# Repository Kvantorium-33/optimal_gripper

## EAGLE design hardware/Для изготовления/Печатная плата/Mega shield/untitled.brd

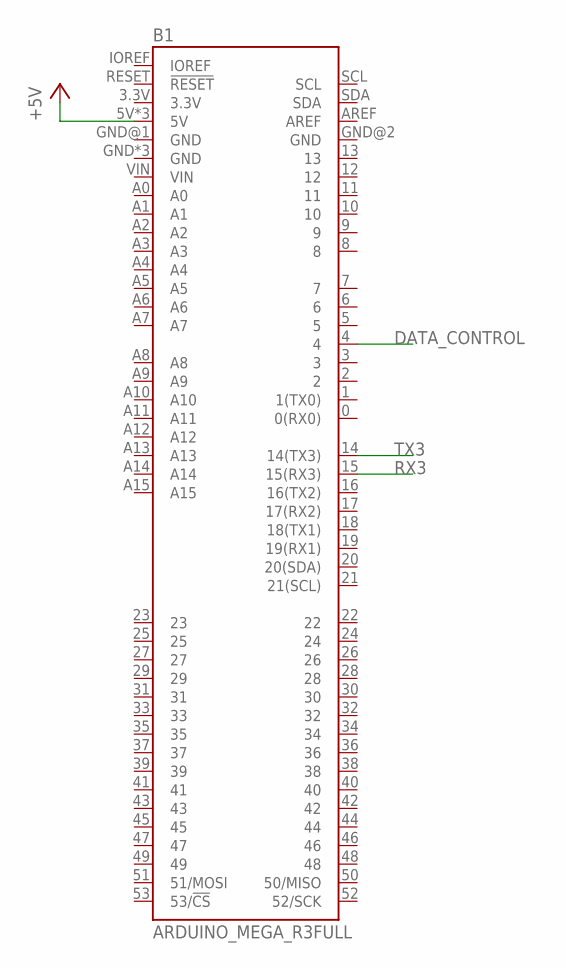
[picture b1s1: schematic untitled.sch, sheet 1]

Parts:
B1: ARDUINO_MEGA_R3FULL; ARDUINO_MEGA_NO_SILK

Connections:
+5V: B1.5V, B1.5V@1 (5V), B1.5V@2 (5V); also elsewhere on the board
DATA_CONTROL: B1.4; also elsewhere on the board
RX3: B1.15 (15(RX3)); also elsewhere on the board
TX3: B1.14 (14(TX3)); also elsewhere on the board

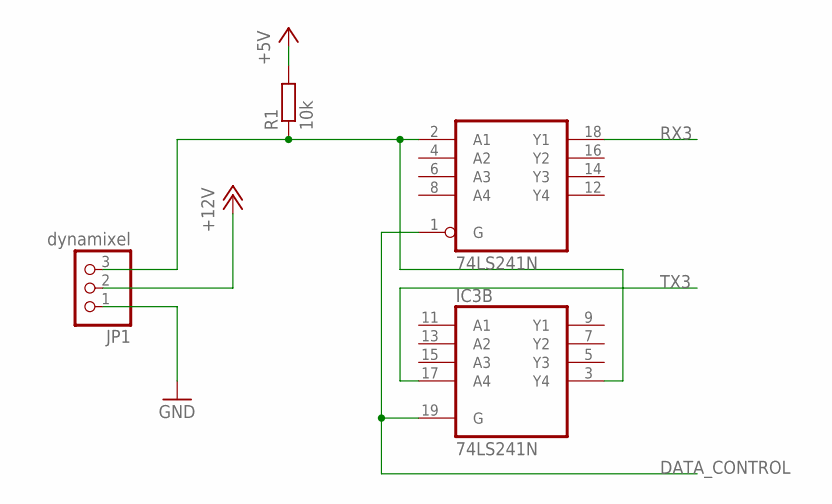
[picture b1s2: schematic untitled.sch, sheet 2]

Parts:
IC3: 74LS241N; DIL20
JP1: dynamixel; 1X03
R1: 10k; 0207/10

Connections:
+5V: R1.2; also elsewhere on the board
+12V: JP1.2
DATA_CONTROL: IC3.1 (G), IC3.19 (G); also elsewhere on the board
GND: IC3.10 (GND), JP1.1
unnamed: IC3.2 (A1), IC3.3 (Y4), JP1.3, R1.1
RX3: IC3.18 (Y1); also elsewhere on the board
TX3: IC3.17 (A4); also elsewhere on the board
VCC: IC3.20 (VCC)

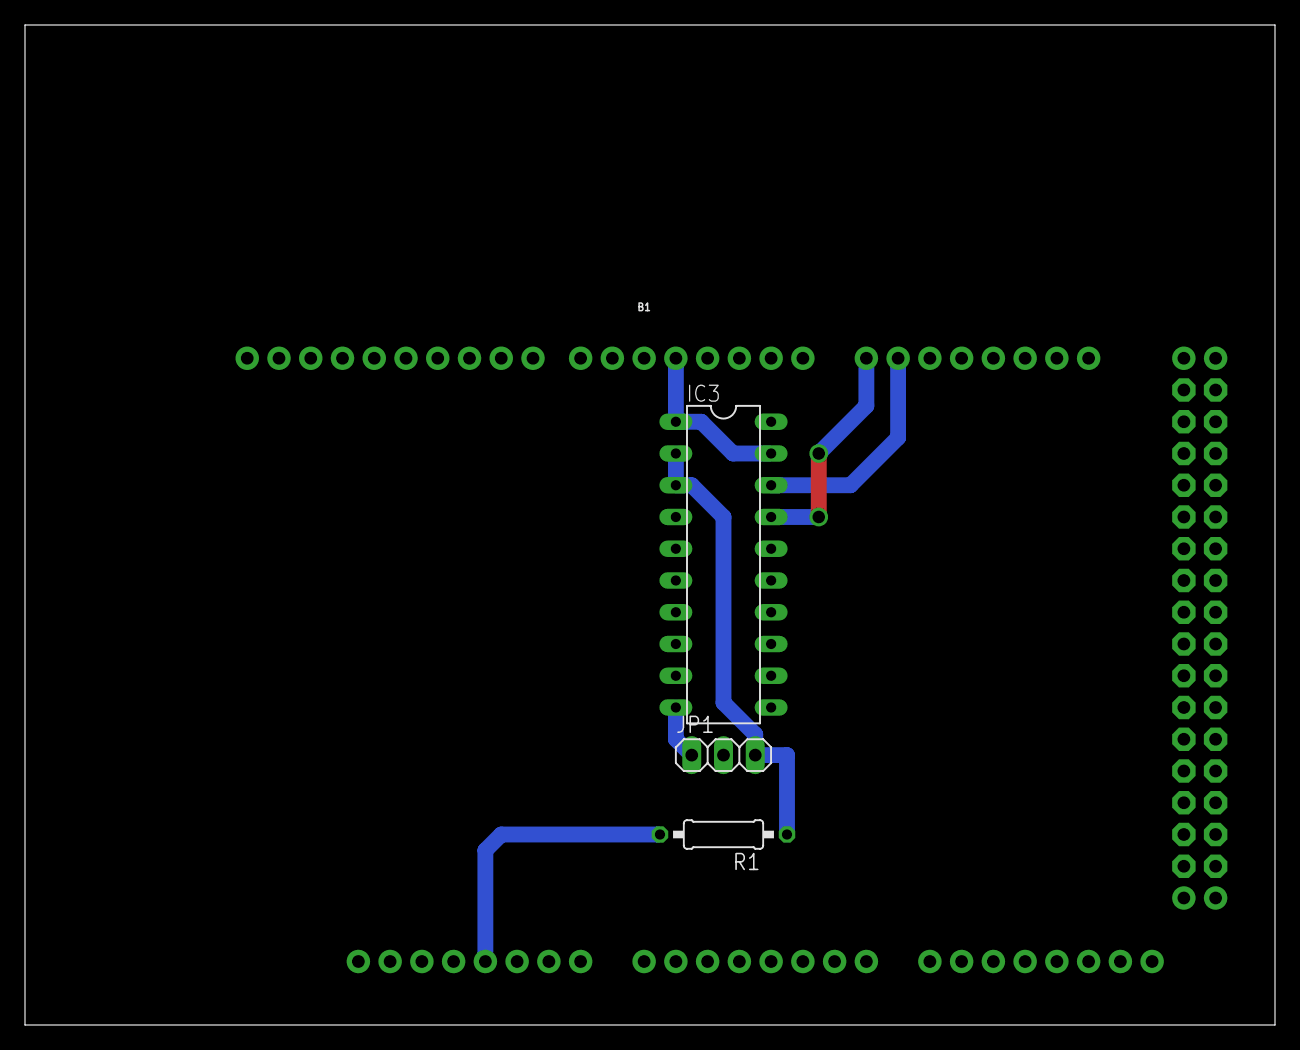
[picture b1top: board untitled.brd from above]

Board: 2 copper layers, 100.0 x 80.0 mm, 4 parts (0 on the bottom side), 6 nets.

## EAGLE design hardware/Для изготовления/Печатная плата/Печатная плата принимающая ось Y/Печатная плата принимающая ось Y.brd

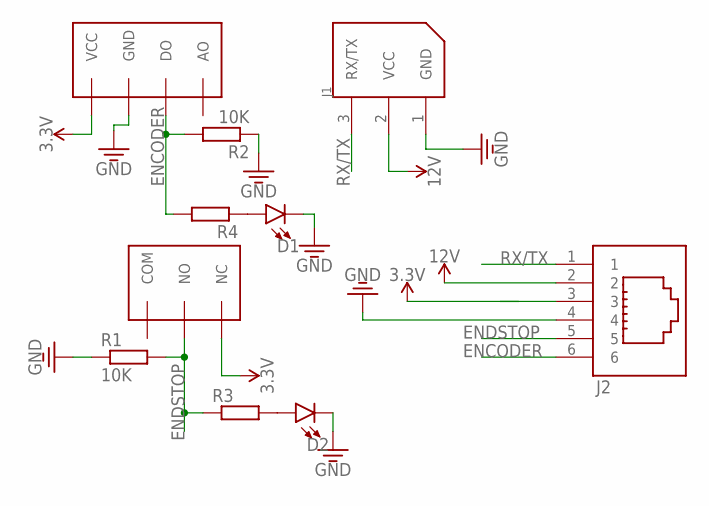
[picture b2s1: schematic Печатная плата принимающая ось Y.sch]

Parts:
D1, D2: LED5MM; LED_5MM
J1: 22-03-5035; 5267-3
J2: 615006138421
R1, R2: 10K; 0204/7
R3, R4: R-EU_0204/7; 0204/7
U$1: OPTICAL_ENCODER_FC-01
U$2: ENDSTOP

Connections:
3.3V: J2.3, U$1.VCC, U$2.NC
12V: J1.2 (VCC), J2.2
ENCODER: J2.6, R2.2, R4.2, U$1.DO
ENDSTOP: J2.5, R1.2, R3.1, U$2.NO
GND: D1.K (C), D2.K (C), J1.1 (GND), J2.4, R1.1, R2.1, U$1.GND
unnamed: D2.A, R3.2
unnamed: D1.A, R4.1
RX/TX: J1.3 (RX/TX), J2.1

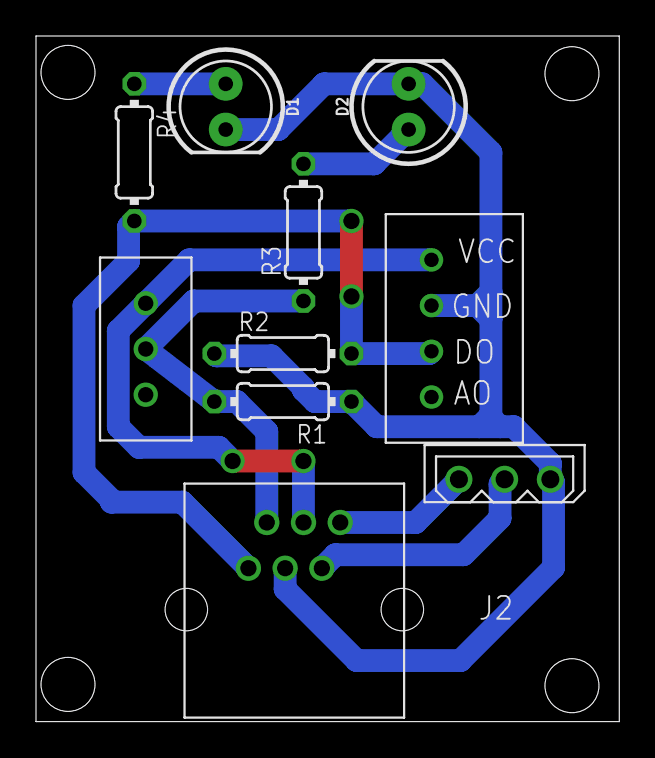
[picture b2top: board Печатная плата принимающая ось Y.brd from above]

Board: 2 copper layers, 32.4 x 38.1 mm, 10 parts (0 on the bottom side), 8 nets.

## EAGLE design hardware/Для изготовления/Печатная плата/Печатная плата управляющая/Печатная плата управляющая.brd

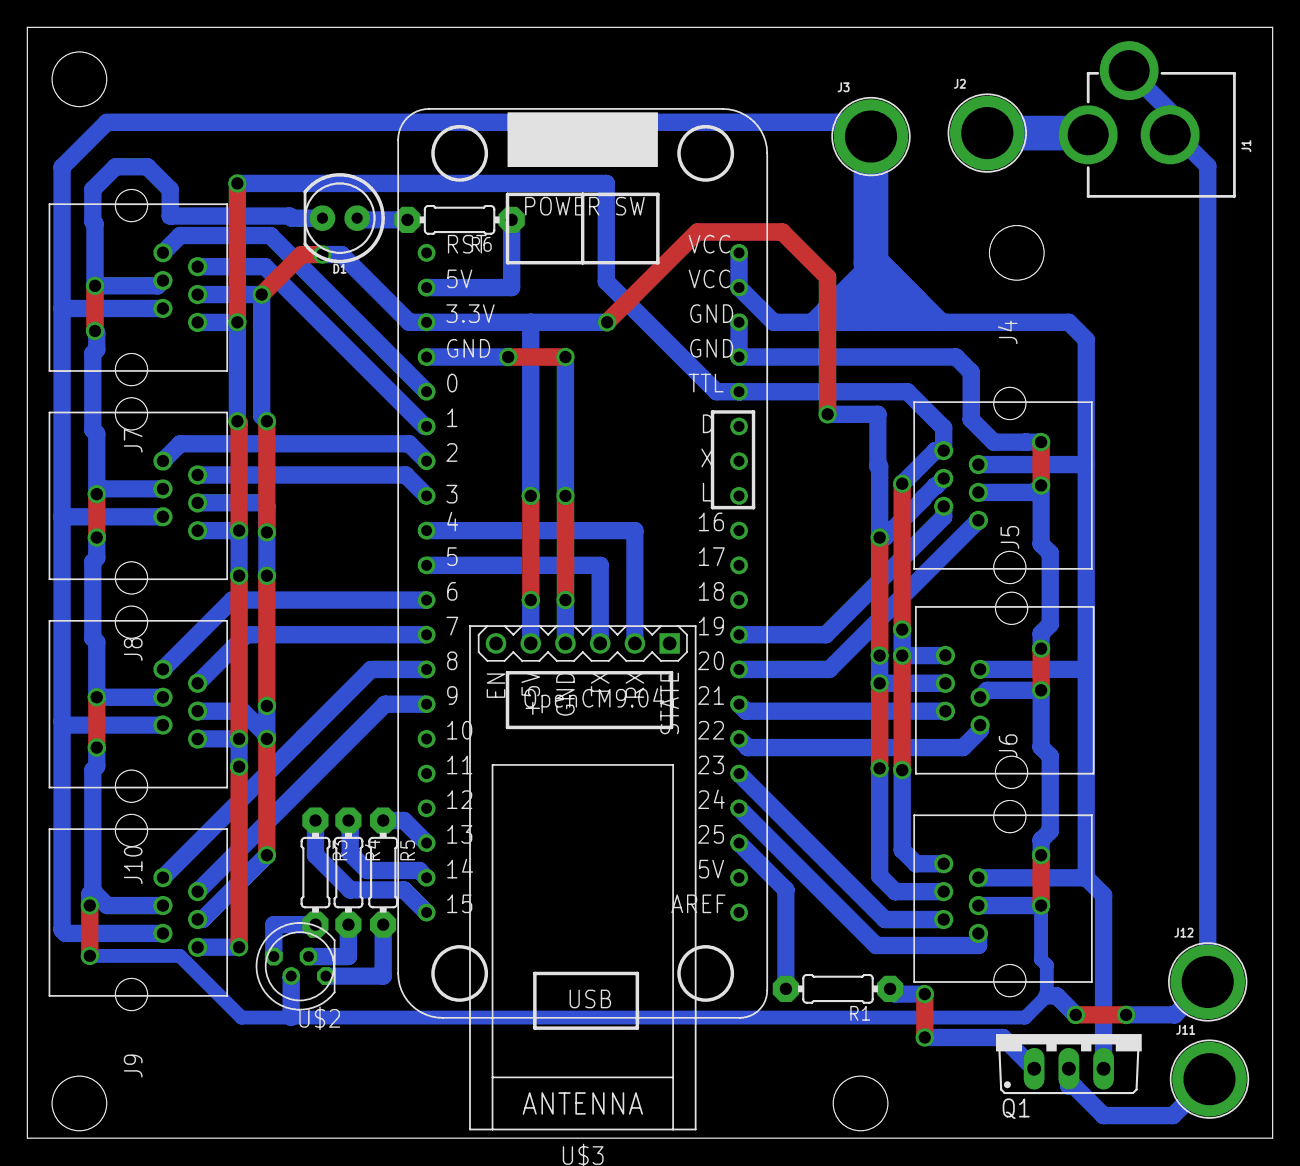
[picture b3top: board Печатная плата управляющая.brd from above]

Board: 2 copper layers, 91.1 x 81.3 mm, 22 parts (0 on the bottom side), 32 nets.

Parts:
D1: LED_5MM
J1: POWER_JACK; POWER_JACK_PTH
J2, J3, J11, J12: BANANA_CONN
J4, J5, J6, J7, J8, J9, J10: 615006138421
Q1: IRF540; TO220BV
R1: 100; 0204/7
R3, R4, R5, R6: 330; 0204/7
U$1: OPENCM9.04
U$2: 5MMRGBLED; LED5MMRGB
U$3: WIRELESS-BLUETOOTH-HC-05

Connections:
3.3V: J4.3, J5.3, J6.3, J7.3, J8.3, J9.3, J10.3, U$1.3.3V, U$3.5
5V: R6.1, U$1.5V, U$1.5V2
12V: J3.P$1, J4.2, J5.2, J6.2, J7.2, J8.2, J9.2, J10.2, Q1.S, U$1.VCC, U$1.VCC2
BLUE: R5.1, U$1.13
ENCODER_X_1: J4.6, U$1.20
ENCODER_X_2: J5.6, U$1.22
ENCODER_Y: J6.6, U$1.24
ENCODER_Z_1: J7.6, U$1.0
ENCODER_Z_2: J8.6, U$1.2
ENCODER_Z_3: J10.6, U$1.6
ENCODER_Z_4: J9.6, U$1.8
ENDSTOP_X_1: J4.5, U$1.19
ENDSTOP_X_2: J5.5, U$1.21
ENDSTOP_Y: J6.5, U$1.23
ENDSTOP_Z_1: J7.5, U$1.1
ENDSTOP_Z_2: J8.5, U$1.3
ENDSTOP_Z_3: J10.5, U$1.7
ENDSTOP_Z_4: J9.5, U$1.9
GND: D1.K, J1.GND, J1.GNDBREAK, J4.4, J5.4, J6.4, J7.4, J8.4, J9.4, J10.4, J12.P$1, U$1.GND, U$1.GND2, U$1.GND3, U$2.P$3, U$3.4
GREEN: R4.1, U$1.14
unnamed: J11.P$1, Q1.D
unnamed: R4.2, U$2.P$2
unnamed: Q1.G, R1.1
unnamed: R5.2, U$2.P$1
unnamed: R3.2, U$2.P$4
unnamed: D1.A, R6.2
unnamed: J1.PWR, J2.P$1
PUMP: R1.2, U$1.25
RED: R3.1, U$1.15
RX2: U$1.5, U$3.3
RX/TX: J4.1, J5.1, J6.1, J7.1, J8.1, J9.1, J10.1, U$1.TTL
TX2: U$1.4, U$3.2

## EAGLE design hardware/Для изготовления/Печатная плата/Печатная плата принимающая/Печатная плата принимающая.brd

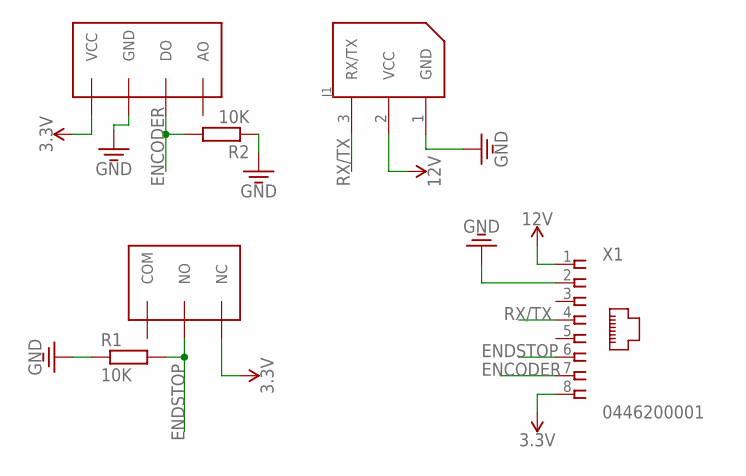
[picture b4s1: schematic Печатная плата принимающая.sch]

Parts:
J1: 22-03-5035; 5267-3
R1, R2: 10K; 0204/7
U$1: OPTICAL_ENCODER_FC-01
U$2: ENDSTOP
X1: 0446200001

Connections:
3.3V: U$1.VCC, U$2.NC, X1.8
12V: J1.2 (VCC), X1.1
ENCODER: R2.2, U$1.DO, X1.7
ENDSTOP: R1.2, U$2.NO, X1.6
GND: J1.1 (GND), R1.1, R2.1, U$1.GND, X1.2
RX/TX: J1.3 (RX/TX), X1.4

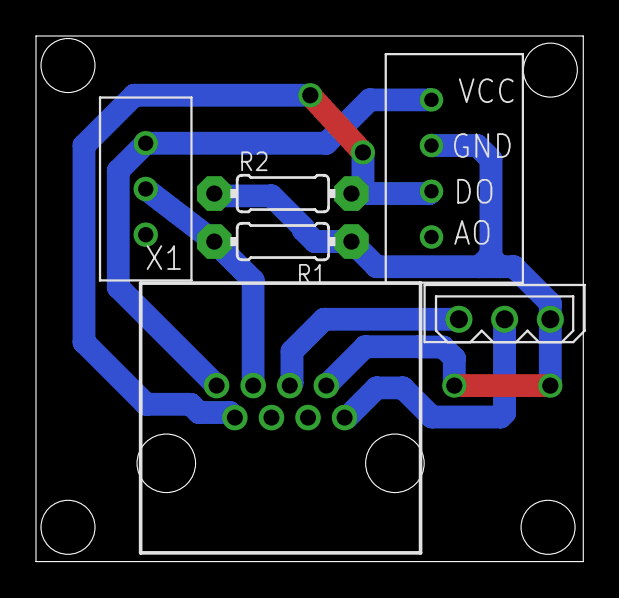
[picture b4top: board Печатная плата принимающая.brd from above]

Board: 2 copper layers, 30.4 x 29.2 mm, 6 parts (0 on the bottom side), 6 nets.

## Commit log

2019-07-16 Добавлены 3D модели
2019-07-16 Подвинул
2019-07-16 1. Изменены каретки
    2. Изменена конструкция манипулятора
    3. Добавлен станочный профиль 30х30х728
2019-07-16 Сортирующая ячейка
2019-07-16 Изменена конструкция кареток оси Х
2019-07-16 Исправлен недочет Фиксатора каретки
2019-07-17 изменена щека каретки
2019-07-17 щека каретки
2019-07-17 Обновлена "сортирующая ячейка"
2019-07-17 Поправлены "Свойства Inventor" деталей
2019-07-18 Added tensorflow ROS package
2019-07-18 изменена сборка
2019-07-18 изменена каретка
2019-07-21 изменена каретка
    центральное отверстие d=8,2
2019-07-21 Создана каретка захвата
    изменены каретка оси Х
    обновлена сборка
2019-08-02 Добавлена опора держателя катка
2019-08-02 изменены каретки оси Z и Y
2019-08-04 изменена основная сборка, созданы крепления для ремней у щек кареток
2019-08-05 Remove tf and vision_msgs submodules
2019-08-05 Add tf_object_detector and vision_msgs as source files
2019-08-05 Remove readme.md
2019-08-05 Change camera
2019-08-05 Add tf model
2019-08-05 Using local object_detector libraries
2019-08-05 изменены крепления под моторы, на Dynamixel AX-12A
2019-08-06 изменен держатель мотора
2019-08-06 изменена сборка держателя мотора, изменен шкив
2019-08-06 добавлены концевики на держатели моторов
2019-08-08 прошивка без ROS
2019-08-08 Создана каретка оси X
2019-08-08 программа для управления динамикселями
2019-08-08 изменена каретка оси X
2019-08-11 Добавлен корпус блока управления
2019-08-13 Убран блок управления
2019-08-13 изменен крепеж ремня
2019-08-13 изменена каретка оси Y
2019-08-14 изменена каретка Y
2019-08-14 Наложены ограничения на передвижения кареток по всем осям
2019-08-18 Добавлен захват
    изменен держатель ремня
2019-08-18 изменен крепеж ремня каретки Y
2019-08-19 изменен зажим ремня
2019-08-19 Исправлены ошибки каретки оси Y
2019-08-20 изменен прижим ремня
2019-08-22 изменены крепежи моторов оси Z
2019-08-22 Изменена сборка
    Добавлена плата принимающая
2019-08-23 Изменена плата принимающая под ось Z
2019-08-24 Изменена управляющая плата
2019-08-25 Добавлен клапан впускной
2019-08-25 Изменена программа
2019-08-27 принимающие платы разделены по осям
2019-08-27 Добавлена отзеркаленная принимающая плата оси Z
2019-08-29 Добавлен ROS пакет распознавания речи
2019-08-29 Добавлена папка "документация"
    добавлен держатель присоски
2019-08-30 Добавлены чертежи
2019-09-22 Add urdf_tutorial files
2019-09-22 Add smart_gripper package
2019-10-25 Обновлена сборка
2019-10-25 Добавлена новая прошивка
    Пока не работает
2019-10-26 добавлен словарь
2019-10-26 Захват переделан на подшипники
2019-10-26 Обновлен захват под винт М4
2019-10-30 Добавлен держатель для плат
2019-10-30 Изменен крепеж платы
2019-10-30 изменена основа блока управления
2019-10-31 Прошивка разделена для OpenCM и Arduino
2019-11-02 Добавлена программа для Arduino mega
    Программа не работает
2019-11-04 изменена программа под arduino mega
    программа не работает
2019-11-05 Изменена прошивка
2019-11-07 Изменена прошивка. Добавлен чек-лист для отправления
    Программа компилируется. Чек-лист может измениться
2019-11-08 Исправлены ошибки прошивки
    нереализовано прерывание на 1 из пинов
2019-11-09 Добавлена поддержка прерываний на 4 пине
2019-11-13 Изменен блок управления
2019-11-15 Добавлен шаблон прошивки для STM32duino
2019-11-16 изменена программа для STM32duino
2019-11-18 Начата новая прогамма для STM32duino
2019-11-19 Добавлены комментарии к программе для STM32duino
2019-11-19 Изменена программа. Работают энкодеры и концевики
2019-11-19 Изменена программа. Добавлена заглушка на оси X
    Великая сила не подключена
2019-11-22 В программе добавлены функции для перемещения осей Z и Y
2019-11-23 Исправлены ошибки программы
2019-11-23 Изменена программа(добавлены новые функции)
2019-11-23 Изменена программа(добавлены новые функции)
    необходимо обновить библиотеку DynamixelSerial3
2019-11-24 Изменена папка прошивки
2019-11-24 Изменена библиотека управления динамикселями
2019-11-26 Добавлена функция движения по координатам
2019-11-28 Исправлена прошивка
2019-11-29 Добавлены ограничители по оси Z
2019-11-29 изменен координатный метод
2019-11-30 Исправлен координатный метод
2019-12-01 Исправлены недочеты программы
2019-12-02 Изменен метод передвижения
2019-12-04 Добавлена функция изменения скорости моторов

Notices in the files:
parts and their libraries:
SparkFun-Boards: Licensing: Creative Commons ShareAlike 4.0 International - https://creativecommons.org/licenses/by-sa/4.0
Wurth_Elektronik_Electromechanic_Input-O: Copyright: Würth Elektronik
